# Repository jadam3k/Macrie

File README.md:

# Macrie

## Overview
This project is a custom macro pad with custom RP2040 MCU :)). It combines a fully designed CAD model, electronics, and firmware into a nice project (i think). The design includesenclosure, PCB, and hardware.

## Why I Made This
It looks like Ai but i really want to tel about it ;p
I started this project because I wanted to better understand combining MCU'S with other things, and i can focus on cad or writing filmware

## Features
- Just macropad ;)

## 3D Model

READ THAT!!! : You can ask where the cover is. I didn’t add it even though there are mounting holes in the enclosure. I decided not to create a cover because I want to show the project to others without having to take anything off. I know it’s a bit unusual, but that’s the idea... I prefer to present it from a more technical side :).

## PCB

ERRORS

THEY ARE JUST TERMICAL SO CHILL - it won't burn

## Wiring Diagram

## Files Included
This repository contains everything needed to review and reproduce the project:

- `/CAD` – source CAD files and exported STEP model
- `/hardware` – PCB design files and gerbers
- `/Firmware` – take a guess
- `BOM.csv` – bill of materials with links

## How to flash RP2040
You dont have to do anything. use circutpython to flash macropad code and pray it will work. you dont have to do anything. you just flash code using USBC

## Bill of Materials

## BOM

| Name | Purpose | Quantity | Total Cost (USD) | Link | Distributor |
|------|--------|----------|------------------|------|-------------|
| PCB | PCB (i can't send link for PCB for JLCPCB) | 5 | 2.00 | https://plainraw.com/raw/e9d4483de526 | JLCPCB |
| 5.1kΩ ±1% 125mW | Resistor CC1/CC2 | 100 | 0.24 | https://www.lcsc.com/product-detail/C27834.html | LCSC |
| 27Ω ±0.25% 100mW Resistor | Impedance Match | 10 | 0.36 | https://www.lcsc.com/product-detail/C5266071.html | LCSC |
| Crystal 12MHz | Crystal for stable MCU operation | 5 | 1.18 | https://www.lcsc.com/product-detail/C2901628.html | LCSC |
| W25Q128JVSIM TR | Flash memory | 1 | 3.58 | https://www.lcsc.com/product-detail/C401671.html | LCSC |
| AMS1117-3.3 | 5V to 3.3V regulator | 5 | 1.13 | https://www.lcsc.com/product-detail/C6186.html | LCSC |
| C2040 | MCU | 1 | 0.95 | https://www.lcsc.com/product-detail/C2040.html | LCSC |
| 1kΩ 125mW 150V Resistor | Resistor for crystal | 100 | 0.25 | https://www.lcsc.com/product-detail/C95781.html | LCSC |
| USB-C | USB-C for power and data | 5 | 0.92 | https://www.lcsc.com/product-detail/C165948.html | LCSC |
| 10uF ±10% 50V Ceramic Capacitor | Used around AMS1117-3.3 | 5 | 0.24 | https://www.lcsc.com/product-detail/C2932476.html | LCSC |
| 18pF ±5% 50V Ceramic Capacitor | Used with crystal | 100 | 0.67 | https://www.lcsc.com/product-detail/C113825.html | LCSC |
| 100nF ±10% 50V Ceramic Capacitor X7R 0805 | Decoupling capacitors | 50 | 0.31 | https://www.lcsc.com/product-detail/C1711.html | LCSC |
| 1uF ±10% 50V Ceramic Capacitor | Decoupling capacitors | 20 | 0.28 | https://www.lcsc.com/product-detail/C28323.html | LCSC |

Additionally (things I already have at home: rectifier diodes (any kind, preferably 1N4148), Cherry switches (you can find them on AliExpress), and an EC11 encoder, which you can also find on AliExpress). I didn’t include them because I can’t add items on the stasis site that I don’t want to receive grant for.

You can use this all. dont forget to star my work :))

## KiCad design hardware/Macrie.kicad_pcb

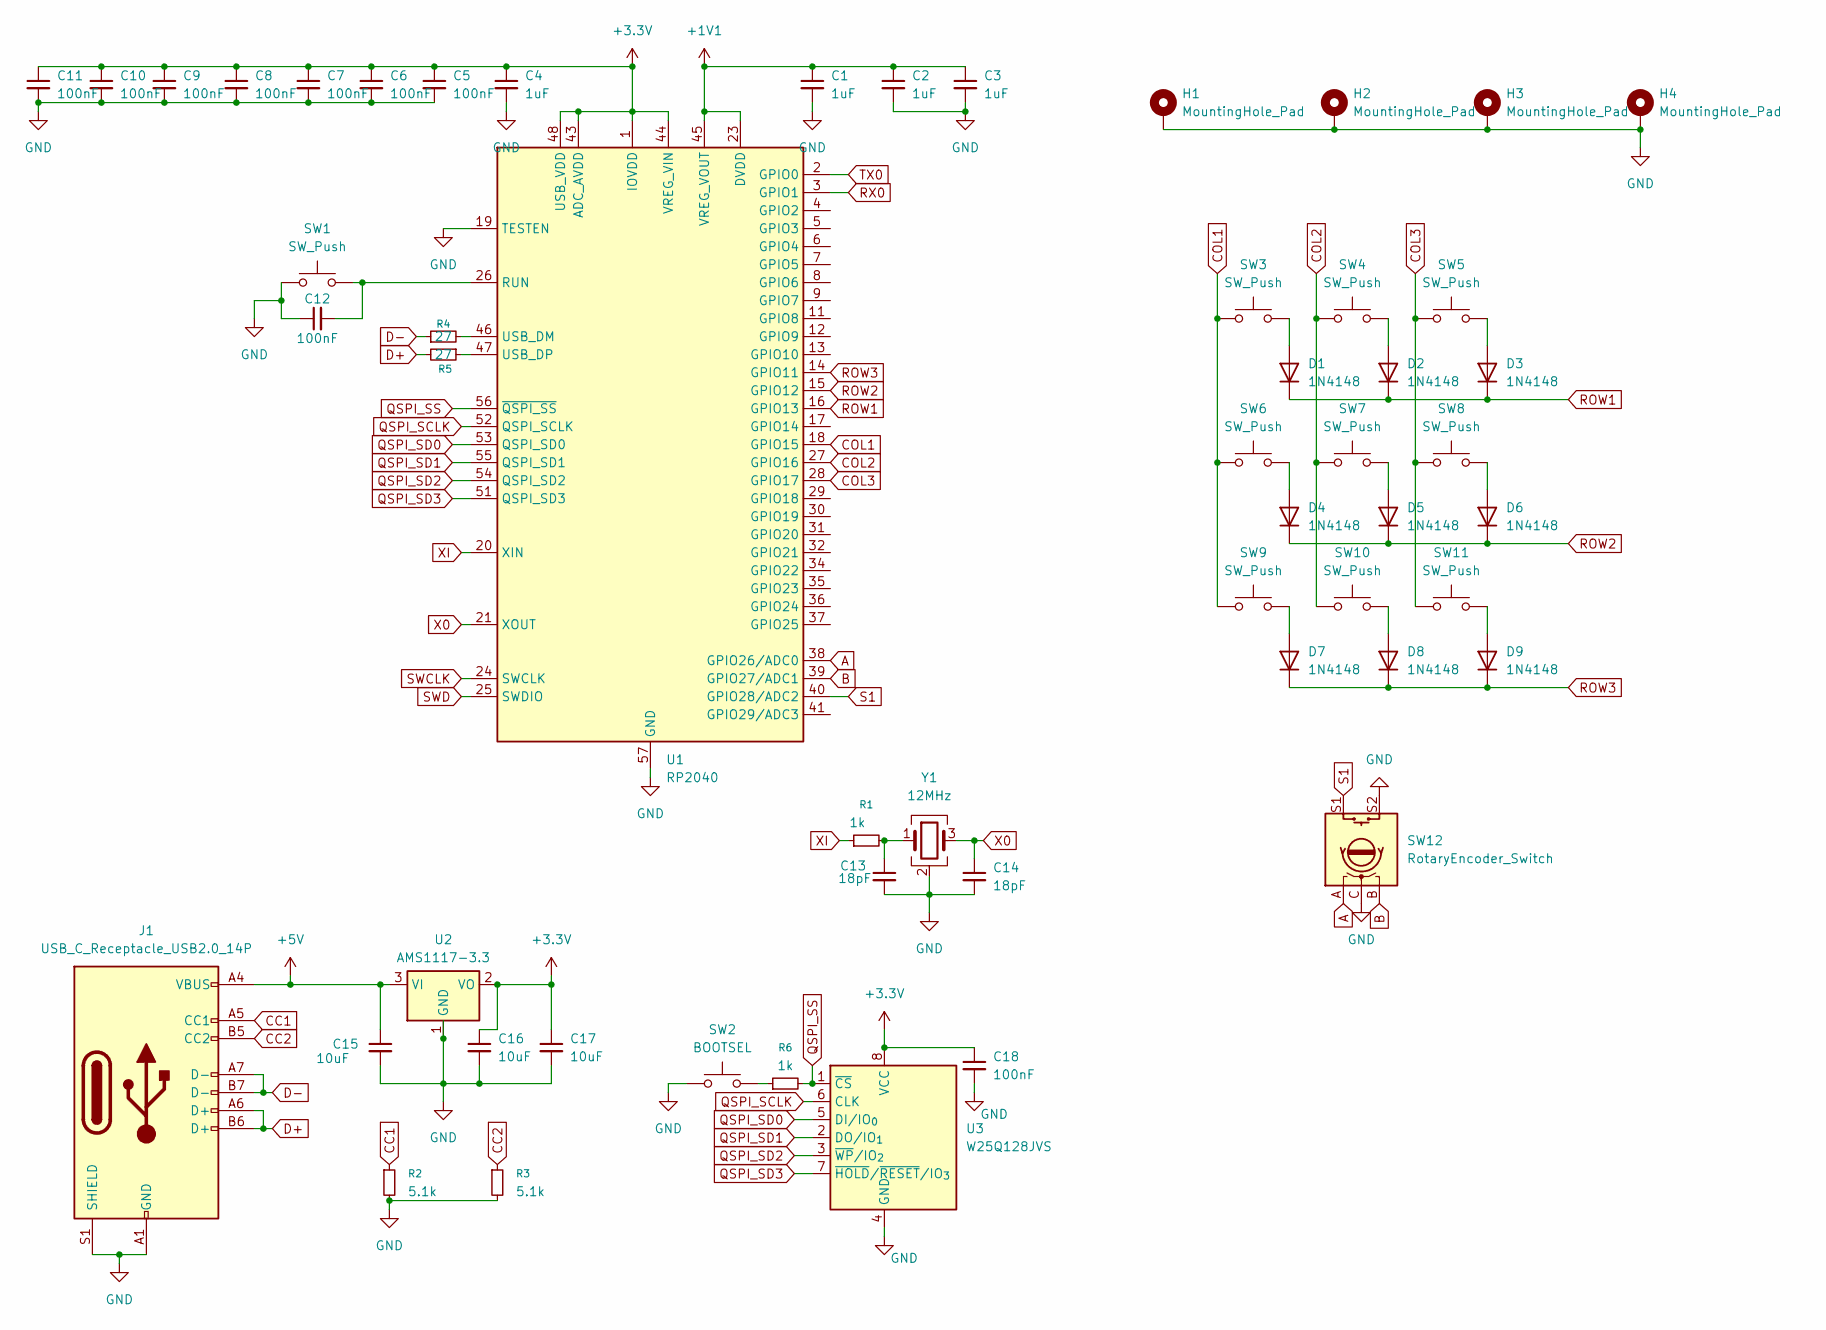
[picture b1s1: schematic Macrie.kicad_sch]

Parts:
C1, C2, C3, C4: 1uF; C_0805_2012Metric_Pad1.18x1.45mm_HandSolder
C5, C6, C7, C8, C9, C10, C11, C12, C18: 100nF; C_0805_2012Metric_Pad1.18x1.45mm_HandSolder
C13, C14: 18pF; C_0805_2012Metric_Pad1.18x1.45mm_HandSolder
C15, C16, C17: 10uF; C_0805_2012Metric_Pad1.18x1.45mm_HandSolder
D1, D2, D3, D4, D5, D6, D7, D8, D9: 1N4148; D_DO-35_SOD27_P7.62mm_Horizontal
H1, H2, H3, H4: MountingHole_Pad; MountingHole_3.2mm_M3
J1: USB_C_Receptacle_USB2.0_14P; USB_C_Receptacle_HRO_TYPE-C-31-M-12
R1, R6: 1k; R_0805_2012Metric_Pad1.20x1.40mm_HandSolder
R2, R3: 5.1k; R_0805_2012Metric_Pad1.20x1.40mm_HandSolder
R4, R5: 27; R_0805_2012Metric_Pad1.20x1.40mm_HandSolder
SW1: SW_Push; SW_Push_SPST_NO_Alps_SKRK
SW2: BOOTSEL; SW_Push_SPST_NO_Alps_SKRK
SW3, SW4, SW5, SW6, SW7, SW8, SW9, SW10, SW11: SW_Push; SW_Cherry_MX_1.00u_PCB
SW12: RotaryEncoder_Switch; RotaryEncoder_Alps_EC11E-Switch_Vertical_H20mm_MountingHoles
U1: RP2040; QFN-56-1EP_7x7mm_P0.4mm_EP3.2x3.2mm
U2: AMS1117-3.3; SOT-223-3_TabPin2
U3: W25Q128JVS; SOIC-8_5.3x5.3mm_P1.27mm
Y1: 12MHz; Crystal_SMD_5032-4Pin_5.0x3.2mm

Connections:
+1V1: C1.1, C2.1, C3.1, U1.23 (DVDD), U1.45 (VREG_VOUT), U1.50 (DVDD)
+3.3V: C4.1, C5.1, C6.1, C7.1, C8.1, C9.1, C10.1, C11.1, C16.1, C17.1, C18.1, U1.1 (IOVDD), U1.10 (IOVDD), U1.22 (IOVDD), U1.33 (IOVDD), U1.42 (IOVDD), U1.43 (ADC_AVDD), U1.44 (VREG_VIN), U1.48 (USB_VDD), U1.49 (IOVDD), U2.2 (VO), U3.8 (VCC)
+5V: C15.1, J1.A4 (VBUS), J1.A9 (VBUS), J1.B4 (VBUS), J1.B9 (VBUS), U2.3 (VI)
A: SW12.A, U1.38 (GPIO26/ADC0)
B: SW12.B, U1.39 (GPIO27/ADC1)
CC1: J1.A5 (CC1), R2.1
CC2: J1.B5 (CC2), R3.1
COL1: SW3.1, SW6.1, SW9.1, U1.18 (GPIO15)
COL2: SW4.1, SW7.1, SW10.1, U1.27 (GPIO16)
COL3: SW5.1, SW8.1, SW11.1, U1.28 (GPIO17)
D+: J1.A6 (D+), J1.B6 (D+), R5.2
D-: J1.A7 (D-), J1.B7 (D-), R4.1
GND: C1.2, C2.2, C3.2, C4.2, C5.2, C6.2, C7.2, C8.2, C9.2, C10.2, C11.2, C12.1, C13.2, C14.2, C15.2, C16.2, C17.2, C18.2, H1.1, H2.1, H3.1, H4.1, J1.A1 (GND), J1.A12 (GND), J1.B1 (GND), J1.B12 (GND), J1.S1 (SHIELD), R2.2, R3.2, SW1.1, SW2.1, SW12.C, SW12.S2, U1.19 (TESTEN), U1.57 (GND), U2.1 (GND), U3.4 (GND), Y1.2 (G), Y1.4 (G)
unnamed: C13.1, R1.2, Y1.1
unnamed: D1.2 (A), SW3.2
unnamed: D2.2 (A), SW4.2
unnamed: D3.2 (A), SW5.2
unnamed: D4.2 (A), SW6.2
unnamed: D5.2 (A), SW7.2
unnamed: D6.2 (A), SW8.2
unnamed: D7.2 (A), SW9.2
unnamed: D8.2 (A), SW10.2
unnamed: D9.2 (A), SW11.2
unnamed: R6.1, SW2.2
unnamed: C12.2, SW1.2, U1.26 (RUN)
unnamed: R4.2, U1.46 (USB_DM)
unnamed: R5.1, U1.47 (USB_DP)
QSPI_SCLK: U1.52 (QSPI_SCLK), U3.6 (CLK)
QSPI_SD0: U1.53 (QSPI_SD0), U3.5 (DI/IO_{0})
QSPI_SD1: U1.55 (QSPI_SD1), U3.2 (DO/IO_{1})
QSPI_SD2: U1.54 (QSPI_SD2), U3.3 (~WP/IO_{2})
QSPI_SD3: U1.51 (QSPI_SD3), U3.7 (~HOLD/~RESET/IO_{3})
QSPI_SS: R6.2, U1.56 (~QSPI_SS), U3.1 (~CS)
ROW1: D1.1 (K), D2.1 (K), D3.1 (K), U1.16 (GPIO13)
ROW2: D4.1 (K), D5.1 (K), D6.1 (K), U1.15 (GPIO12)
ROW3: D7.1 (K), D8.1 (K), D9.1 (K), U1.14 (GPIO11)
RX0: U1.3 (GPIO1)
S1: SW12.S1, U1.40 (GPIO28/ADC2)
SWCLK: U1.24 (SWCLK)
SWD: U1.25 (SWDIO)
TX0: U1.2 (GPIO0)
X0: C14.1, U1.21 (XOUT), Y1.3
XI: R1.1, U1.20 (XIN)

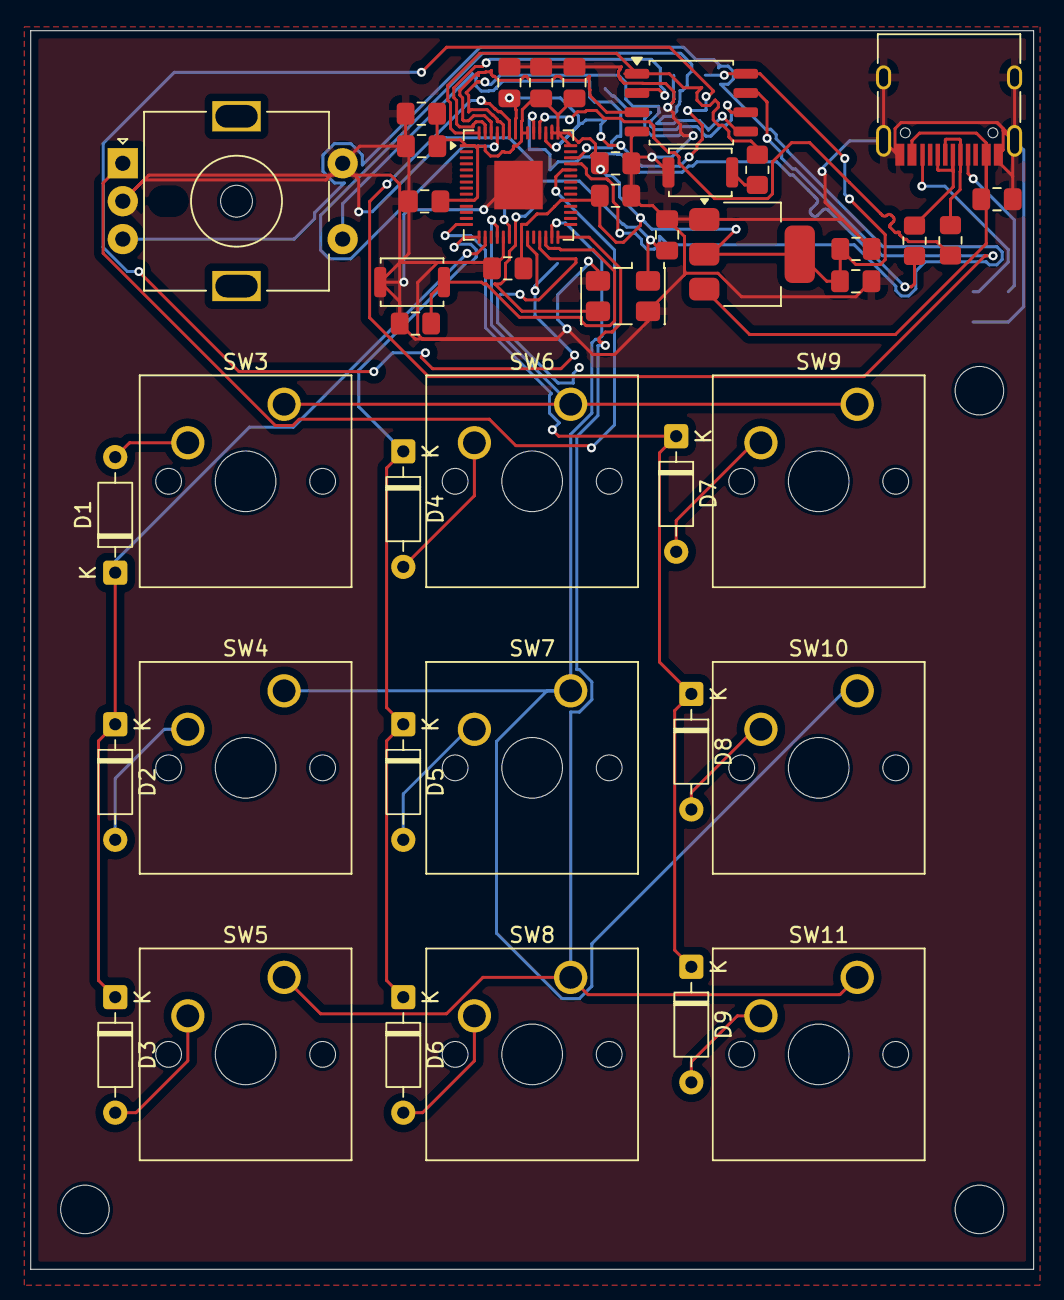
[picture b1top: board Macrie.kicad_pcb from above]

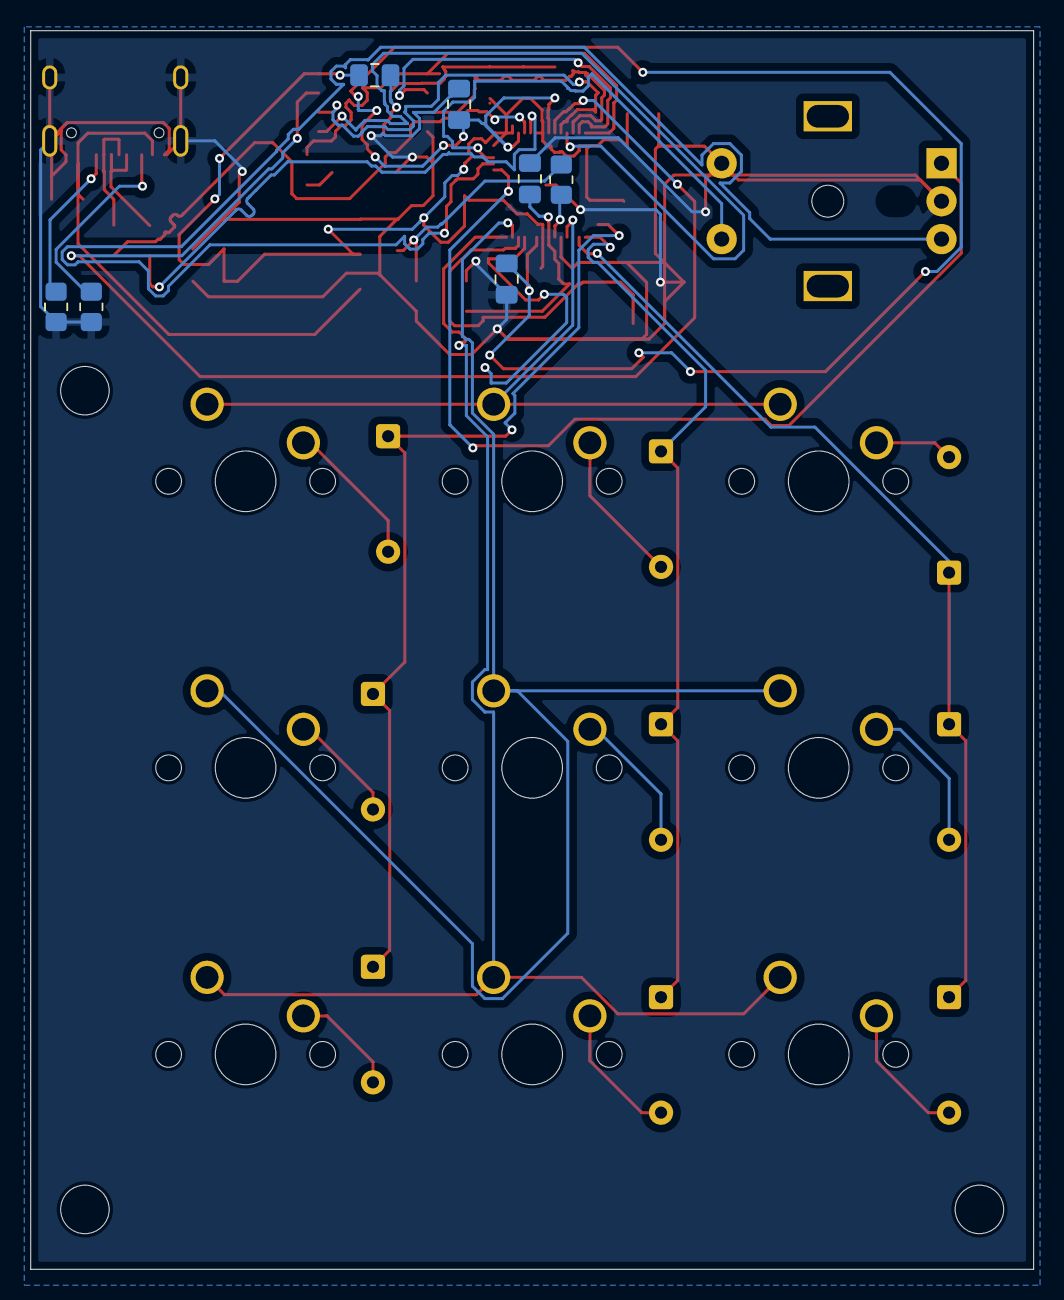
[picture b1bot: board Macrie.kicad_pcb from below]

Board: 2 copper layers, 66.2 x 81.7 mm, 53 parts (7 on the bottom side), 39 nets.

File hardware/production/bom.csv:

Designator,Footprint,Quantity,Value,LCSC Part #
"C1, C2, C3, C4",0805,4,1uF,
"C10, C11, C12, C18, C5, C6, C7, C8, C9",0805,9,100nF,
"C13, C14",0805,2,18pF,
"C15, C16, C17",0805,3,10uF,
"D1, D2, D3, D4, D5, D6, D7, D8, D9",D_DO-35_SOD27_P7.62mm_Horizontal,9,1N4148,
J1,USB_C_Receptacle_HRO_TYPE-C-31-M-12,1,USB_C_Receptacle_USB2.0_14P,
"R1, R6",0805,2,1k,
"R2, R3",0805,2,5.1k,
"R4, R5",0805,2,27,
SW1,SW_Push_SPST_NO_Alps_SKRK,1,SW_Push,
"SW10, SW11, SW3, SW4, SW5, SW6, SW7, SW8, SW9",SW_Cherry_MX_1.00u_PCB,9,SW_Push,
SW12,RotaryEncoder_Alps_EC11E-Switch_Vertical_H20mm_MountingHoles,1,RotaryEncoder_Switch,
SW2,SW_Push_SPST_NO_Alps_SKRK,1,BOOTSEL,
U1,QFN-56-1EP_7x7mm_P0.4mm_EP3.2x3.2mm,1,RP2040,
U2,SOT-223-3_TabPin2,1,AMS1117-3.3,
U3,SOIC-8_5.3x5.3mm_P1.27mm,1,W25Q128JVS,
Y1,Crystal_SMD_5032-4Pin_5.0x3.2mm,1,12MHz,

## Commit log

2026-03-27 Update BOM.csv with new capacitor and notes
    Added a note about additional components at home and included a capacitor entry.
